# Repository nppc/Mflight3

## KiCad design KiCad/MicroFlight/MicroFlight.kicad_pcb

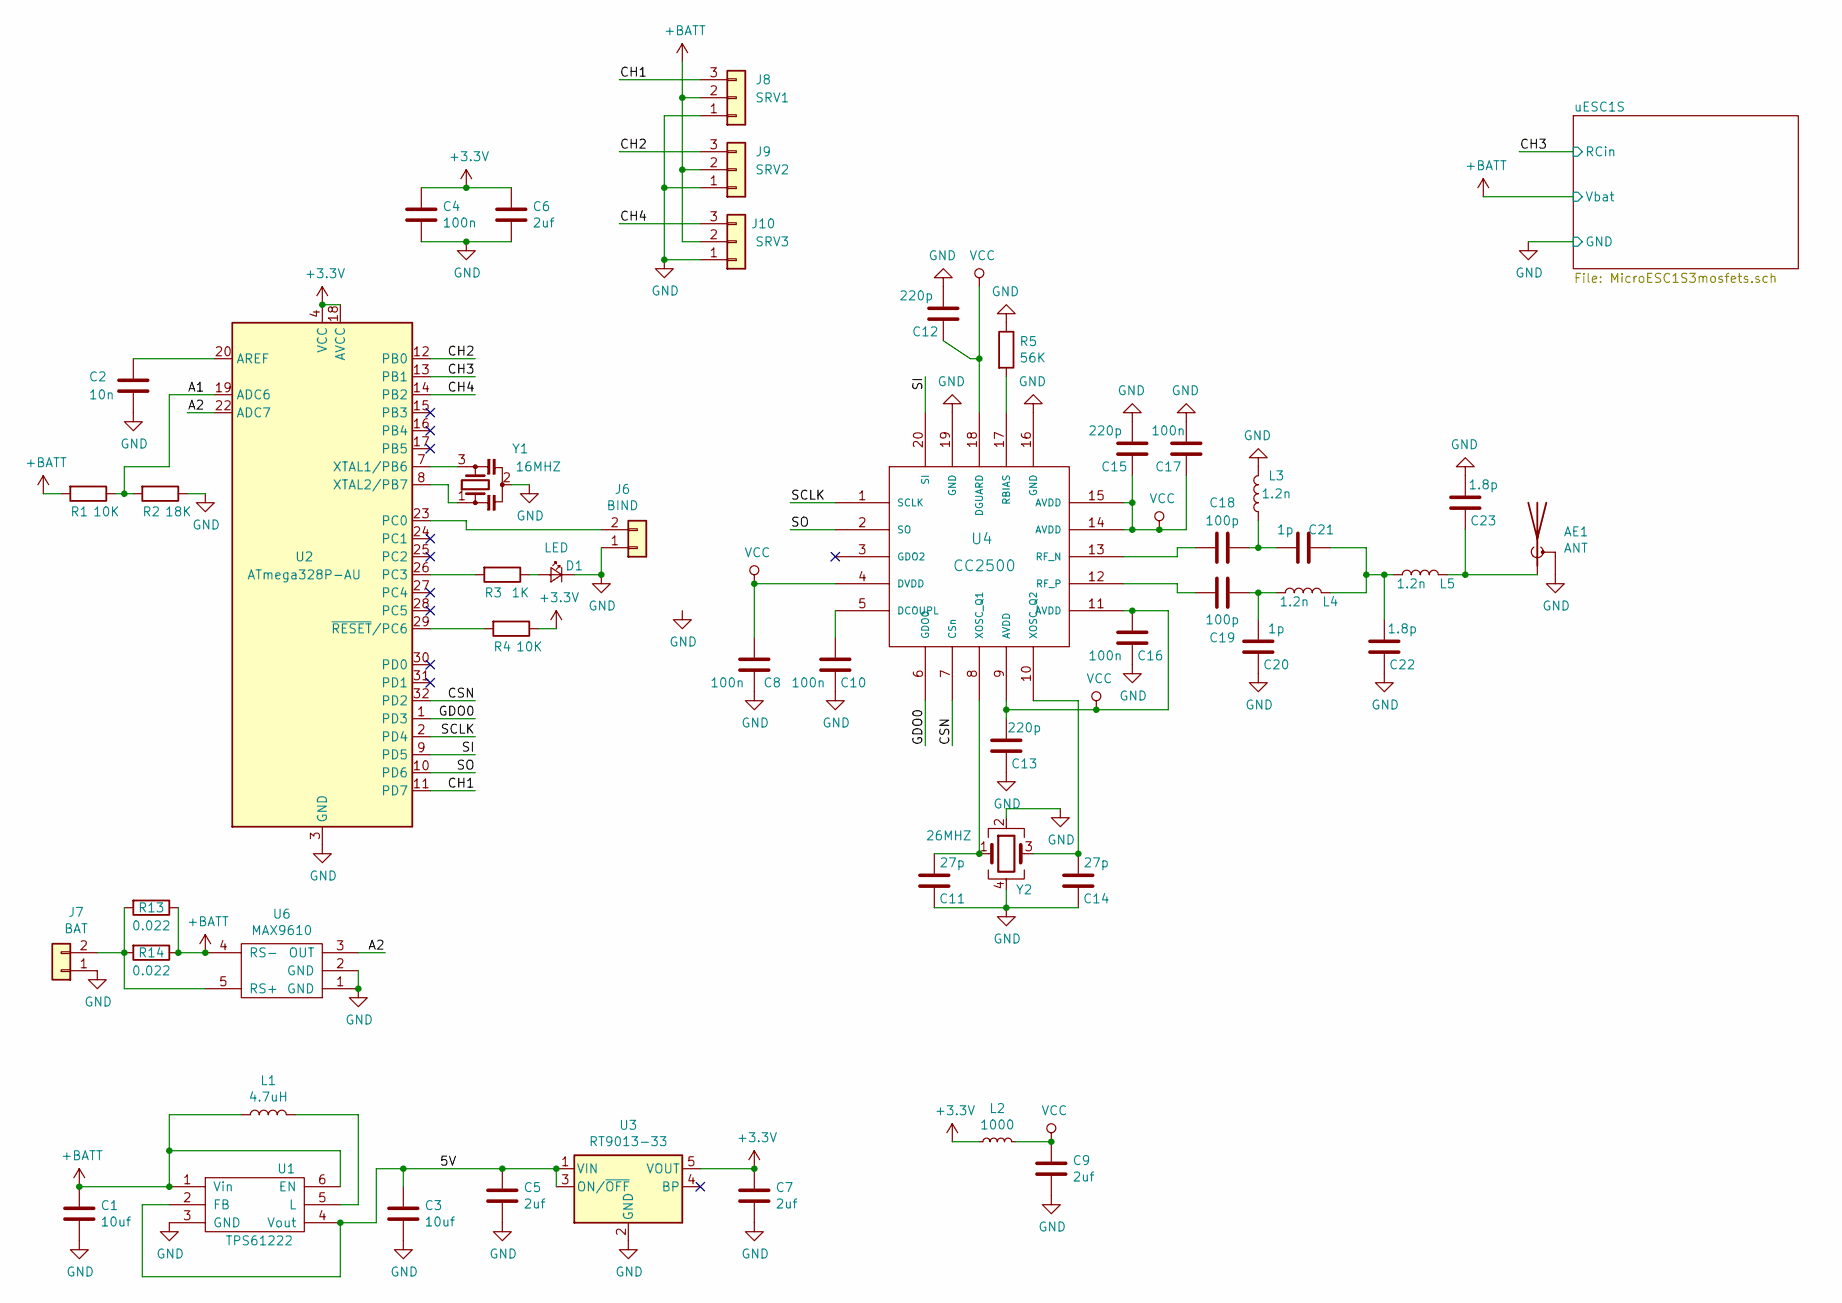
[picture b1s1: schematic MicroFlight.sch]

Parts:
AE1: ANT; ANT_PCB
C1, C3: 10uf; C_0603
C2: 10n; C_0603
C4: 100n; C_0603
C5, C6, C7, C9: 2uf; C_0603
C8, C10, C16, C17: 100n; C_0402
C11, C14: 27p; C_0402
C12, C13, C15: 220p; C_0402
C18, C19: 100p; C_0402
C20, C21: 1p; C_0402
C22, C23: 1.8p; C_0402
D1: LED; LED_0603
J6: BIND; Conn2pin_small
J7: BAT; Conn_1x02_2.54mm
J8: SRV1; Pin_Header_Straight_1x03_Pitch1.27mm
J9: SRV2; Pin_Header_Straight_1x03_Pitch1.27mm
J10: SRV3; Pin_Header_Straight_1x03_Pitch1.27mm
L1: 4.7uH; InductorXFL2006
L2: 1000; L_0603
L3, L4, L5: 1.2n; L_0402
R1, R4: 10K; R_0603
R2: 18K; R_0603
R3: 1K; R_0603
R5: 56K; R_0402_NoSilk
R13: 0.022; R_1206
R14: 0.022; R_2010
U1: TPS61222; SC-70-6
U2: ATmega328P-AU; TQFP-32_7x7mm_Pitch0.8mm
U3: RT9013-33; SOT-23-5
U4: CC2500
U6: MAX9610; SOT-353_SC-70-5
Y1: 16MHZ; Ceramic_Resonator_SMD_3mm
Y2: 26MHZ; Crystal_SMD_SeikoEpson_FA238-4pin_3.2x2.5mm

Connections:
+3V3: C4.1, C6.1, C7.1, L2.1, R4.1, U2.4 (VCC), U2.6 (VCC), U2.18 (AVCC), U3.5 (VOUT)
+BATT: C1.1, J8.2, J9.2, J10.2, L1.1, R1.2, R13.1, R14.1, U1.1 (Vin), U1.6 (EN), U6.4 (RS-); also elsewhere on the board
/5V: C3.1, C5.1, U1.2 (FB), U1.4 (Vout), U3.1 (VIN), U3.3 (ON/~OFF~)
/A1: R1.1, R2.2, U2.19 (ADC6)
/A2: U2.22 (ADC7), U6.3 (OUT)
/CH1: J8.3, U2.11 (PD7)
/CH2: J9.3, U2.12 (PB0)
/CH3: U2.13 (PB1); also elsewhere on the board
/CH4: J10.3, U2.14 (PB2)
/CSN: U2.32 (PD2), U4.7 (CSn)
/GDO0: U2.1 (PD3), U4.6 (GDO0)
/SCLK: U2.2 (PD4), U4.1 (SCLK)
/SI: U2.9 (PD5), U4.20 (SI)
/SO: U2.10 (PD6), U4.2 (SO)
GND: AE1.2 (Shield), C1.2, C2.2, C3.2, C4.2, C5.2, C6.2, C7.2, C8.1, C9.2, C10.1, C11.1, C12.2, C13.1, C14.1, C15.2, C16.1, C17.1, C20.1, C22.1, C23.1, D1.1 (K), J6.1, J7.1, J8.1, J9.1, J10.1, L3.2, R2.1, R5.1, U1.3 (GND), U2.3 (GND), U2.5 (GND), U2.21 (GND), U3.2 (GND), U4.16 (GND), U4.19 (GND), U6.1 (GND), U6.2 (GND), Y1.2, Y2.2, Y2.4; also elsewhere on the board
unnamed: AE1.1 (A), C23.2, L5.2
unnamed: C2.1, U2.20 (AREF)
unnamed: C10.2, U4.5 (DCOUPL)
unnamed: C11.2, U4.8 (XOSC_Q1), Y2.1
unnamed: C14.2, U4.10 (XOSC_Q2), Y2.3
unnamed: C18.1, C21.2, L3.1
unnamed: C18.2, U4.13 (RF_N)
unnamed: C19.1, C20.2, L4.1
unnamed: C19.2, U4.12 (RF_P)
unnamed: C21.1, C22.2, L4.2, L5.1
unnamed: D1.2 (A), R3.1
unnamed: J6.2, U2.23 (PC0)
unnamed: J7.2, R13.2, R14.2, U6.5 (RS+)
unnamed: L1.2, U1.5 (L)
unnamed: R3.2, U2.26 (PC3)
unnamed: R4.2, U2.29 (~RESET~/PC6)
unnamed: R5.2, U4.17 (RBIAS)
unnamed: U2.7 (XTAL1/PB6), Y1.3
unnamed: U2.8 (XTAL2/PB7), Y1.1
VCC: C8.2, C9.1, C12.1, C13.2, C15.1, C16.2, C17.2, L2.2, U4.4 (DVDD), U4.9 (AVDD), U4.11 (AVDD), U4.14 (AVDD), U4.15 (AVDD), U4.18 (DGUARD)

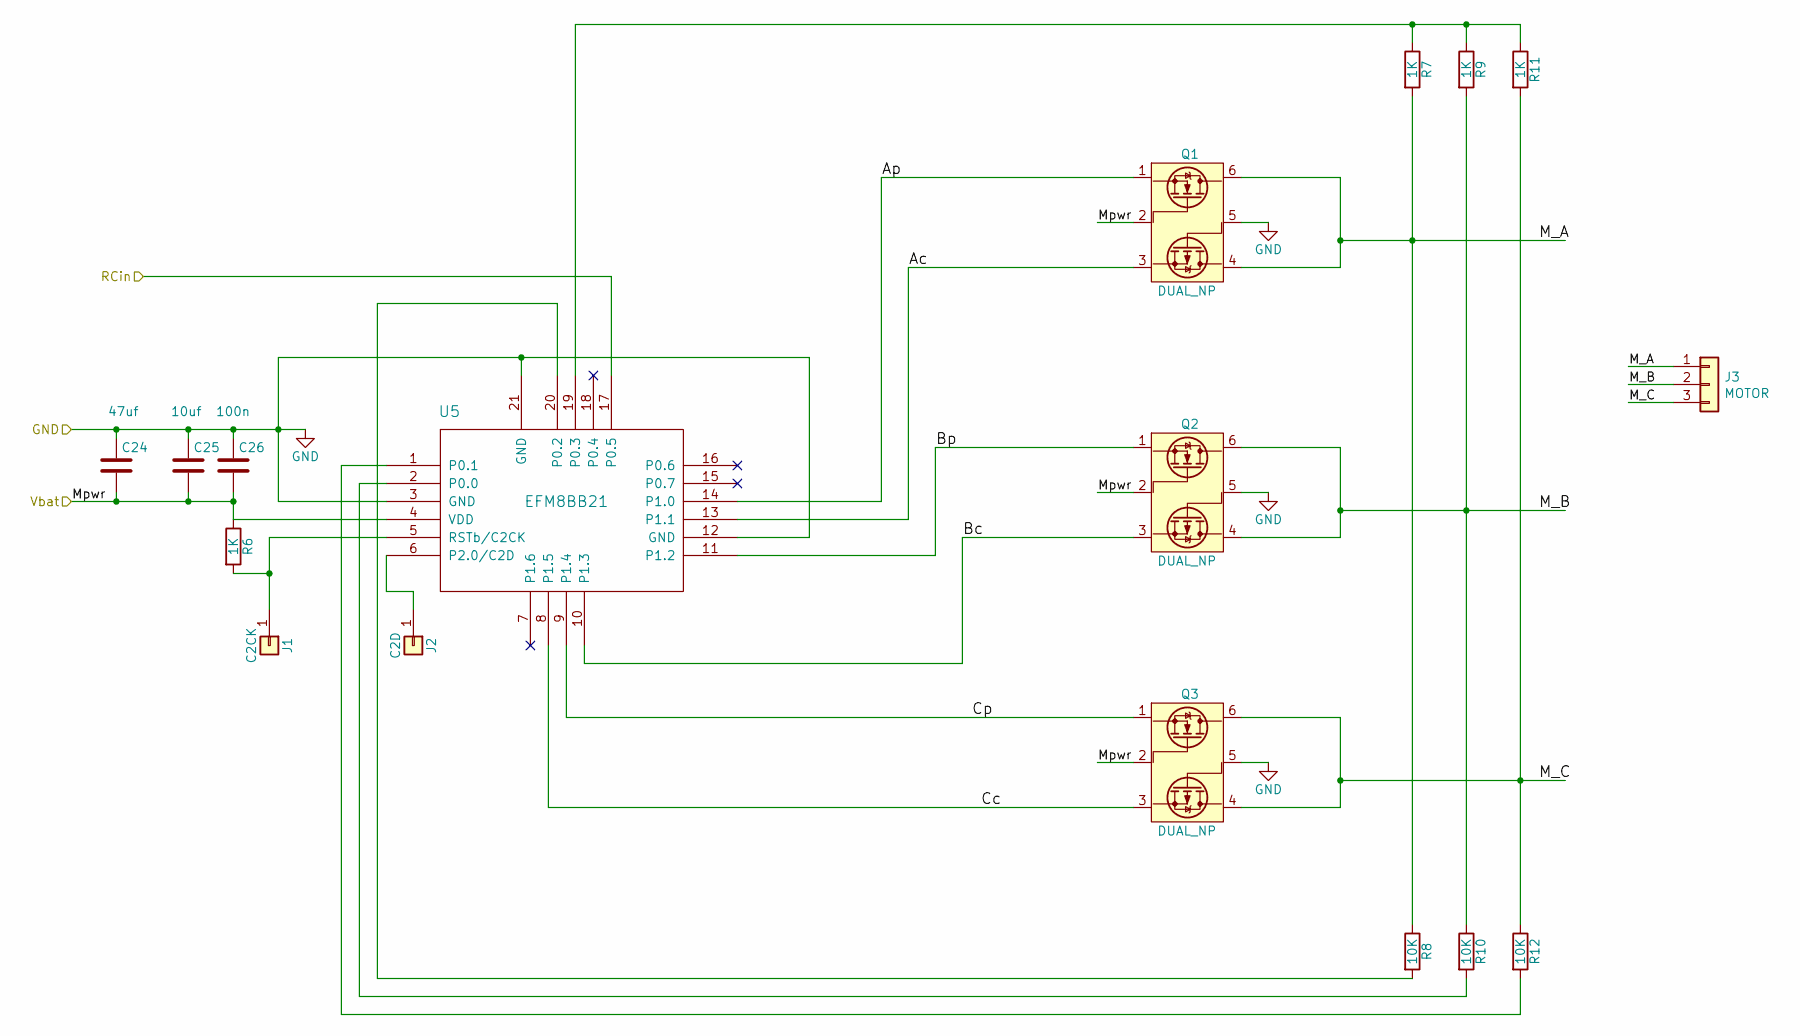
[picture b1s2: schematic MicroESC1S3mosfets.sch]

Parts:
C24: 47uf; C_0603
C25: 10uf; C_0402
C26: 100n; C_0402
J1: C2CK; PAD_1.2X0.6_Round
J2: C2D; PAD_1.2X0.6_Round
J3: MOTOR; Molex_PicoBlade_53047-0310_03x1.25mm_Straight
Q1, Q2, Q3: DUAL_NP; SuperSOT-6
R6, R7, R9, R11: 1K; R_0402_NoSilk
R8, R10, R12: 10K; R_0402_NoSilk
U5: EFM8BB21; QFN20

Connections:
+BATT: C24.2, C25.2, C26.2, Q1.2 (G1), Q2.2 (G1), Q3.2 (G1), R6.1, U5.4 (VDD); also elsewhere on the board
/CH3: U5.17 (P0.5); also elsewhere on the board
/uESC1S/Ac: Q1.3 (D2), U5.13 (P1.1)
/uESC1S/Ap: Q1.1 (S1), U5.14 (P1.0)
/uESC1S/Bc: Q2.3 (D2), U5.10 (P1.3)
/uESC1S/Bp: Q2.1 (S1), U5.11 (P1.2)
/uESC1S/Cc: Q3.3 (D2), U5.8 (P1.5)
/uESC1S/Cp: Q3.1 (S1), U5.9 (P1.4)
/uESC1S/M_A: J3.1, Q1.4 (S2), Q1.6 (D1), R7.2, R8.1
/uESC1S/M_B: J3.2, Q2.4 (S2), Q2.6 (D1), R9.2, R10.1
/uESC1S/M_C: J3.3, Q3.4 (S2), Q3.6 (D1), R11.2, R12.1
GND: C24.1, C25.1, C26.1, Q1.5 (G2), Q2.5 (G2), Q3.5 (G2), U5.3 (GND), U5.12 (GND), U5.21 (GND); also elsewhere on the board
unnamed: J1.1, R6.2, U5.5 (RSTb/C2CK)
unnamed: J2.1, U5.6 (P2.0/C2D)
unnamed: R8.2, U5.20 (P0.2)
unnamed: R10.2, U5.2 (P0.0)
unnamed: R7.1, R9.1, R11.1, U5.19 (P0.3)
unnamed: R12.2, U5.1 (P0.1)

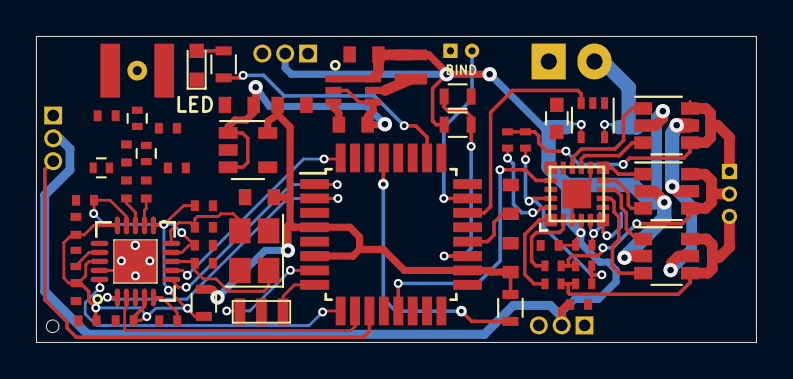
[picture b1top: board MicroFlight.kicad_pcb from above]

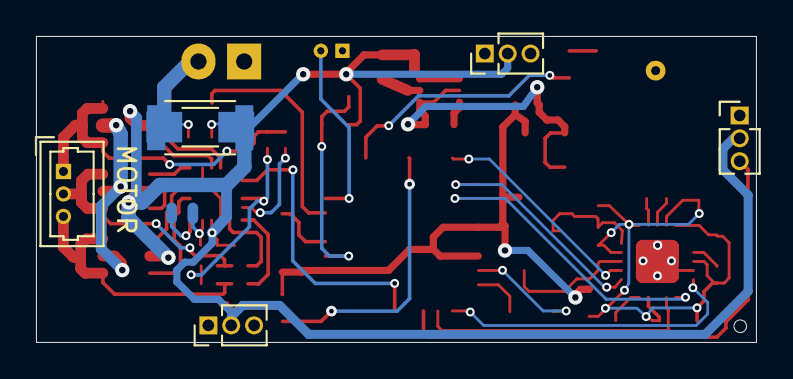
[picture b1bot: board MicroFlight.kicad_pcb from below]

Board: 2 copper layers, 40.0 x 17.0 mm, 66 parts (8 on the bottom side), 50 nets.

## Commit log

2019-12-15 PCB draft
2019-12-17 PCB - added optional shunt for current sensing
2019-12-17 PCB - pdf
2019-12-18 PCB ready
